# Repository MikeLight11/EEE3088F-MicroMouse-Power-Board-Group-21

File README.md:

# Micromouse Power Subsystem

## Overview
This repository contains the design files and documentation for the power subsystem of a micromouse robot developed for the EEE3088F 2025 course project. The micromouse is an autonomous robot designed to navigate through and solve mazes efficiently. The power subsystem is responsible for powering the entire micromouse, including battery management, motor control, and regulated power distribution.

## Project Description
The micromouse project consists of four main modules:
- Motherboard (provided)
- Processor (provided)
- Sensing system (provided)
- Power subsystem (this project)

Our power subsystem is designed to meet the following key requirements:
- Power and control 4 motors bidirectionally
- Provide battery monitoring via INA219 on I2C bus
- Charge the battery from 9V input with dual charging modes
- Integrate USB-C with 9V output
- Provide external load switching capabilities
- Deliver regulated 3.3V and 5V outputs
- Include ON/OFF switch with ultra-low power standby mode

## Features
- **Battery Management**: Uses BQ24074 charge controller for efficient Li-Ion battery charging with configurable charging currents (200mA standard, 600mA fast charging)
- **Motor Control**: H-bridges for bidirectional control of up to 4 motors
- **Power Regulation**: Provides stable 3.3V and 5V power rails
- **Load Switching**: Two external load switches capable of handling 1A each
- **Battery Monitoring**: INA219 current/voltage monitoring over I2C
- **Power-saving Mode**: <30μA current draw in OFF state
- **USB-C Integration**: Supports power input through USB-C

## Repository Structure
- `/Docs` - Documentation including the report
- `/Final Schematic and PCB` - KiCad schematic files and PCB design files
- `/Footprint Library` - Contains all imported footprints 
- `/Gerbers` - Production Gerber files
- `/Old Schematics` - Backup KiCad schematic files 
- `/Production files` - Contains the zip file of the Gerbers, the BOM and CPL (JLCPCB Submission files)

## Hardware Specifications
- Dimensions: Maximum 82mm × 60mm
- Battery: 3.7V 800mAh LiPo
- Input Voltage: 9V or USB-C
- Output Voltages: 3.3V (300mA max) and 5V (1.5A max)
- PCB Connector: 2x16 (2.54mm pin pitch) header connecting to the motherboard

## 3D render of PCB

## Contributors
- Michael Lighton (LGHMIC003)
- Michael Smith (SMTMIC078)

## Acknowledgments
- University of Cape Town, Department of Electrical Engineering
- EEE3088F course staff

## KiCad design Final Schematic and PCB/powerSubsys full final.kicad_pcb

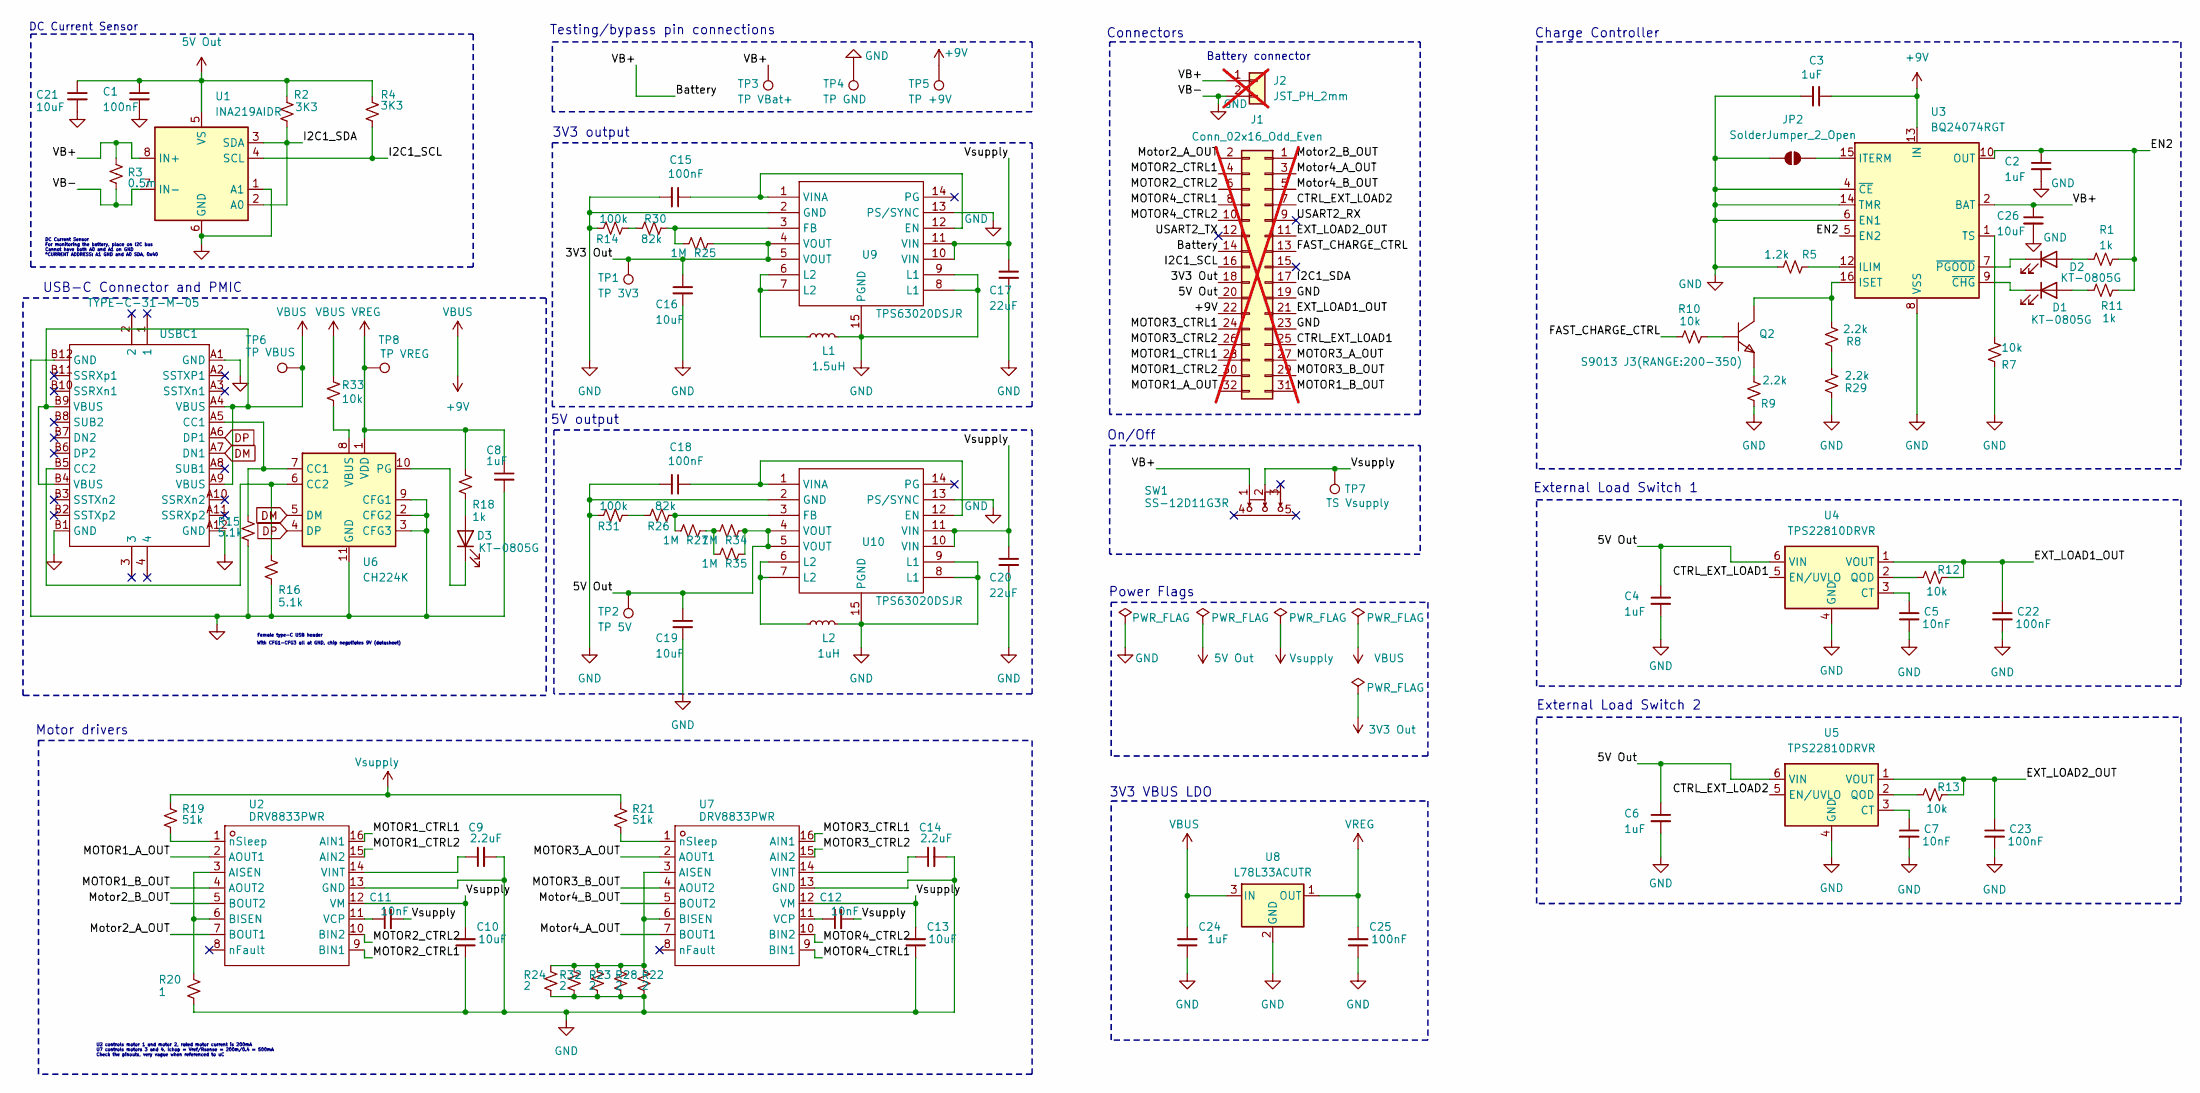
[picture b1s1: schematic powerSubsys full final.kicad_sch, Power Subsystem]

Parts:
C1, C15, C18, C22, C23, C25: 100nF; C0603; LCSC C14663
C2, C3, C4, C6, C8, C24: 1uF; C0805; LCSC C28323
C5, C7, C11, C12: 10nF; C0402; LCSC C15195
C9, C14: 2.2uF; C0805; LCSC C377773
C10, C13, C16, C19, C21, C26: 10uF; C0805; LCSC C15850
C17, C20: 22uF; C1206; LCSC C12891
D1, D2, D3: KT-0805G; LED0805-R-RD; LCSC C2297
J1: Conn_02x16_Odd_Even; PinHeader_2x16_P2.54mm_Vertical; not fitted
J2: JST_PH_2mm; JST_PH_S2B-PH-K_1x02_P2.00mm_Horizontal; not fitted
JP2: SolderJumper_2_Open; SolderJumper-2_P1.3mm_Open_RoundedPad1.0x1.5mm
L1: 1.5uH; L1008; LCSC C98034
L2: 1uH; C0805; LCSC C1042
Q2: S9013 J3(RANGE:200-350); SOT-23-3_L2.9-W1.3-P1.90-LS2.4-BR; MANUFACTURER PART S9013 J3(RANGE:200-350); LCSC PART NAME NPN 电流:500mA 耐压:25V H档(200-350)
R1, R11, R18: 1k; C0603; LCSC C21190
R2, R4: 3K3; C0603; LCSC C22978
R3: 0.5m; R2512; LCSC C469426
R5: 1.2k; C0603; LCSC C22765
R7, R10, R12, R13, R33: 10k; C0805; LCSC C17414
R8, R9, R29: 2.2k; C0603; LCSC C4190
R14, R31: 100k; C1206; LCSC C17900
R15, R16: 5.1k; C0603; LCSC C23186
R19, R21: 51k; C0805; LCSC C17737
R20: 1; C1206; LCSC C17928
R22, R23, R24, R28, R32: 2; C0603; LCSC C22977
R25, R27, R34, R35: 1M; C1206; LCSC C17927
R26, R30: 82k; C0603; LCSC C23254
SW1: SS-12D11G3R; SW-TH_SS-12D11L3; CURRENT RATING (DC) 3A; VOLTAGE RATING (DC) 125V; MANUFACTURER PART SS-12D11G3R; LCSC PART NAME 柄长3mm 弯插双档 滑动开关
TP1: TP 3V3; TestPoint_Pad_D1.5mm
TP2: TP 5V; TestPoint_Pad_D1.5mm
TP3: TP VBat+; TestPoint_Pad_D1.5mm
TP4: TP GND; TestPoint_Pad_D1.5mm
TP5: TP +9V; TestPoint_Pad_D1.5mm
TP6: TP VBUS; TestPoint_Pad_D1.5mm
TP7: TS Vsupply; TestPoint_Pad_D1.5mm
TP8: TP VREG; TestPoint_Pad_D1.5mm
U1: INA219AIDR; SOIC-8_3.9x4.9mm_P1.27mm; LCSC C138706
U2, U7: DRV8833PWR; TSSOP-16_L5.0-W4.4-P0.65-LS6.4-BL; MANUFACTURER PART DRV8833PWR; LCSC PART NAME DRV8833PWR
U3: BQ24074RGT; VQFN-16-1EP_3x3mm_P0.5mm_EP1.6x1.6mm; LCSC C54313
U4, U5: TPS22810DRVR; WSON-6-1EP_2x2mm_P0.65mm_EP1x1.6mm; LCSC C527679
U6: CH224K; SSOP-10-1EP_3.9x4.9mm_P1mm_EP2.1x3.3mm; LCSC C970725
U8: L78L33ACUTR; SOT-89-3; LCSC C14170
U9, U10: TPS63020DSJR; VSON-14_L4.0-W3.0-P0.50-BL-EP_TI_DSJ; INPUT VOLTAGE 1.8V~5.5V; OUTPUT VOLTAGE 1.2V~5.5V; MANUFACTURER PART TPS63020DSJR; LCSC PART NAME 高效率单电感升降压转换器
USBC1: TYPE-C-31-M-05; USB-C-SMD_TYPE-C-USB-19; CURRENT RATING-POWER 5A; MANUFACTURER PART TYPE-C-31-M-05; LCSC PART NAME Type-C 母

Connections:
3V3 Out: C16.1, J1.18, R25.2, TP1.1, U9.4 (VOUT), U9.5 (VOUT)
5V Out: C1.1, C4.1, C6.1, C19.1, C21.1, J1.20, R2.1, R4.1, R34.2, R35.2, TP2.1, U1.5 (VS), U4.6 (VIN), U5.6 (VIN), U10.4 (VOUT), U10.5 (VOUT)
+9V: C3.1, C24.2, J1.22, R33.1, TP5.1, TP6.1, U3.13 (IN), U8.3 (IN), USBC1.A4 (VBUS), USBC1.A9 (VBUS), USBC1.B4 (VBUS), USBC1.B9 (VBUS)
/Battery: C26.1, J1.14, J2.1, R3.1, SW1.1, TP3.1, U1.8 (IN+), U3.2 (BAT), U3.3 (BAT)
/CTRL_EXT_LOAD1: J1.25, U4.5 (EN/UVLO)
/CTRL_EXT_LOAD2: J1.7, U5.5 (EN/UVLO)
/EN2: C2.1, R1.1, R11.1, U3.5 (EN2), U3.10 (OUT), U3.11 (OUT)
/EXT_LOAD1_OUT: C22.1, J1.21, R12.2, U4.1 (VOUT)
/EXT_LOAD2_OUT: C23.1, J1.11, R13.2, U5.1 (VOUT)
/FAST_CHARGE_CTRL: J1.13, R10.1
/I2C1_SCL: J1.16, R4.2, U1.4 (SCL)
/I2C1_SDA: J1.17, R2.2, U1.2 (A0), U1.3 (SDA)
/MOTOR1_A_OUT: J1.32, U2.2 (AOUT1)
/MOTOR1_B_OUT: J1.31, U2.4 (AOUT2)
/MOTOR1_CTRL1: J1.28, U2.16 (AIN1)
/MOTOR1_CTRL2: J1.30, U2.15 (AIN2)
/MOTOR2_CTRL1: J1.4, U2.9 (BIN1)
/MOTOR2_CTRL2: J1.6, U2.10 (BIN2)
/MOTOR3_A_OUT: J1.27, U7.2 (AOUT1)
/MOTOR3_B_OUT: J1.29, U7.4 (AOUT2)
/MOTOR3_CTRL1: J1.24, U7.16 (AIN1)
/MOTOR3_CTRL2: J1.26, U7.15 (AIN2)
/MOTOR4_CTRL1: J1.8, U7.9 (BIN1)
/MOTOR4_CTRL2: J1.10, U7.10 (BIN2)
/Motor2_A_OUT: J1.2, U2.7 (BOUT1)
/Motor2_B_OUT: J1.1, U2.5 (BOUT2)
/Motor4_A_OUT: J1.3, U7.7 (BOUT1)
/Motor4_B_OUT: J1.5, U7.5 (BOUT2)
/USART2_RX: J1.9
/USART2_TX: J1.12
DM: U6.5 (DM), USBC1.A7 (DN1)
DP: U6.4 (DP), USBC1.A6 (DP1)
GND: C1.2, C2.2, C3.2, C4.2, C5.2, C6.2, C7.2, C8.2, C9.2, C10.1, C13.1, C14.2, C15.2, C16.2, C17.2, C18.2, C19.2, C20.2, C21.2, C22.2, C23.2, C24.1, C25.1, C26.2, J1.19, J1.23, J2.2, JP2.1 (A), L1.2, L2.2, R3.2, R5.1, R7.2, R9.2, R14.1, R15.2, R16.2, R20.2, R22.2, R23.2, R24.2, R28.2, R29.2, R31.1, R32.2, TP4.1, U1.1 (A1), U1.6 (GND), U1.7 (IN-), U2.13 (GND), U3.4 (~CE), U3.6 (EN1), U3.8 (VSS), U3.14 (TMR), U3.17 (VSS), U4.4 (GND), U4.7 (GND), U5.4 (GND), U5.7 (GND), U6.2 (CFG2), U6.3 (CFG3), U6.9 (CFG1), U6.11 (GND), U7.13 (GND), U8.2 (GND), U9.2 (GND), U9.8 (L1), U9.9 (L1), U9.13 (PS/SYNC), U9.15 (PGND), U10.2 (GND), U10.8 (L1), U10.9 (L1), U10.13 (PS/SYNC), U10.15 (PGND), USBC1.A1 (GND), USBC1.A12 (GND), USBC1.B1 (GND), USBC1.B12 (GND); also elsewhere on the board
unnamed: D1.2 (A), R11.2
unnamed: D1.1 (K), U3.9 (~CHG)
unnamed: D2.2 (A), R1.2
unnamed: D2.1 (K), U3.7 (~PGOOD)
unnamed: D3.2 (A), R18.2
unnamed: D3.1 (K), U6.10 (PG)
unnamed: JP2.2 (B), U3.15 (ITERM)
unnamed: L1.1, U9.6 (L2), U9.7 (L2)
unnamed: L2.1, U10.6 (L2), U10.7 (L2)
unnamed: Q2.1 (B), R10.2
unnamed: Q2.3 (C), R8.1, U3.16 (ISET)
unnamed: Q2.2 (E), R9.1
unnamed: R14.2, R30.1
unnamed: R26.1, R31.2
unnamed: R27.2, R34.1, R35.1
unnamed: R8.2, R29.1
unnamed: R20.1, U2.3 (AISEN), U2.6 (BISEN)
unnamed: C11.1, U2.11 (VCP)
unnamed: C9.1, U2.14 (VINT)
unnamed: R19.2, U2.1 (nSleep)
unnamed: R5.2, U3.12 (ILIM)
unnamed: R7.1, U3.1 (TS)
unnamed: C5.1, U4.3 (CT)
unnamed: R12.1, U4.2 (QOD)
unnamed: C7.1, U5.3 (CT)
unnamed: R13.1, U5.2 (QOD)
unnamed: R15.1, U6.7 (CC1), USBC1.A5 (CC1)
unnamed: R16.1, U6.6 (CC2), USBC1.B5 (CC2)
unnamed: R33.2, U6.8 (VBUS)
unnamed: R22.1, R23.1, R24.1, R28.1, R32.1, U7.3 (AISEN), U7.6 (BISEN)
unnamed: C12.1, U7.11 (VCP)
unnamed: C14.1, U7.14 (VINT)
unnamed: R21.2, U7.1 (nSleep)
unnamed: C15.1, U9.1 (VINA), U9.12 (EN)
unnamed: R25.1, R30.2, U9.3 (FB)
unnamed: C18.1, U10.1 (VINA), U10.12 (EN)
unnamed: R26.2, R27.1, U10.3 (FB)
VREG: C8.1, C25.2, R18.1, TP8.1, U6.1 (VDD), U8.1 (OUT)
Vsupply: C10.2, C11.2, C12.2, C13.2, C17.1, C20.1, R19.1, R21.1, SW1.2, TP7.1, U2.12 (VM), U7.12 (VM), U9.10 (VIN), U9.11 (VIN), U10.10 (VIN), U10.11 (VIN)

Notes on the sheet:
Battery connector
3V3 VBUS LDO
U2 controls motor 1 and motor 2, rated motor current is 200mA U7 controls motors 3 and 4, Ichop = Vref/Rsense = 200m/0.4 = 500mA Check the pinouts, very vague when referenced to uC
DC Current Sensor
External Load Switch 2
Connectors
DC Current Sensor For monitoring the battery, place on I2C bus Cannot have both A0 and A1 on GND *CURRENT ADDRESS: A1 GND and A0 SDA, 0x40
Power Flags
Motor drivers
Charge Controller
Female type-C USB header
3V3 output
On/Off
5V output
Testing/bypass pin connections
With CFG1-CFG3 all at GND, chip negotiates 9V (datasheet)
External Load Switch 1
USB-C Connector and PMIC

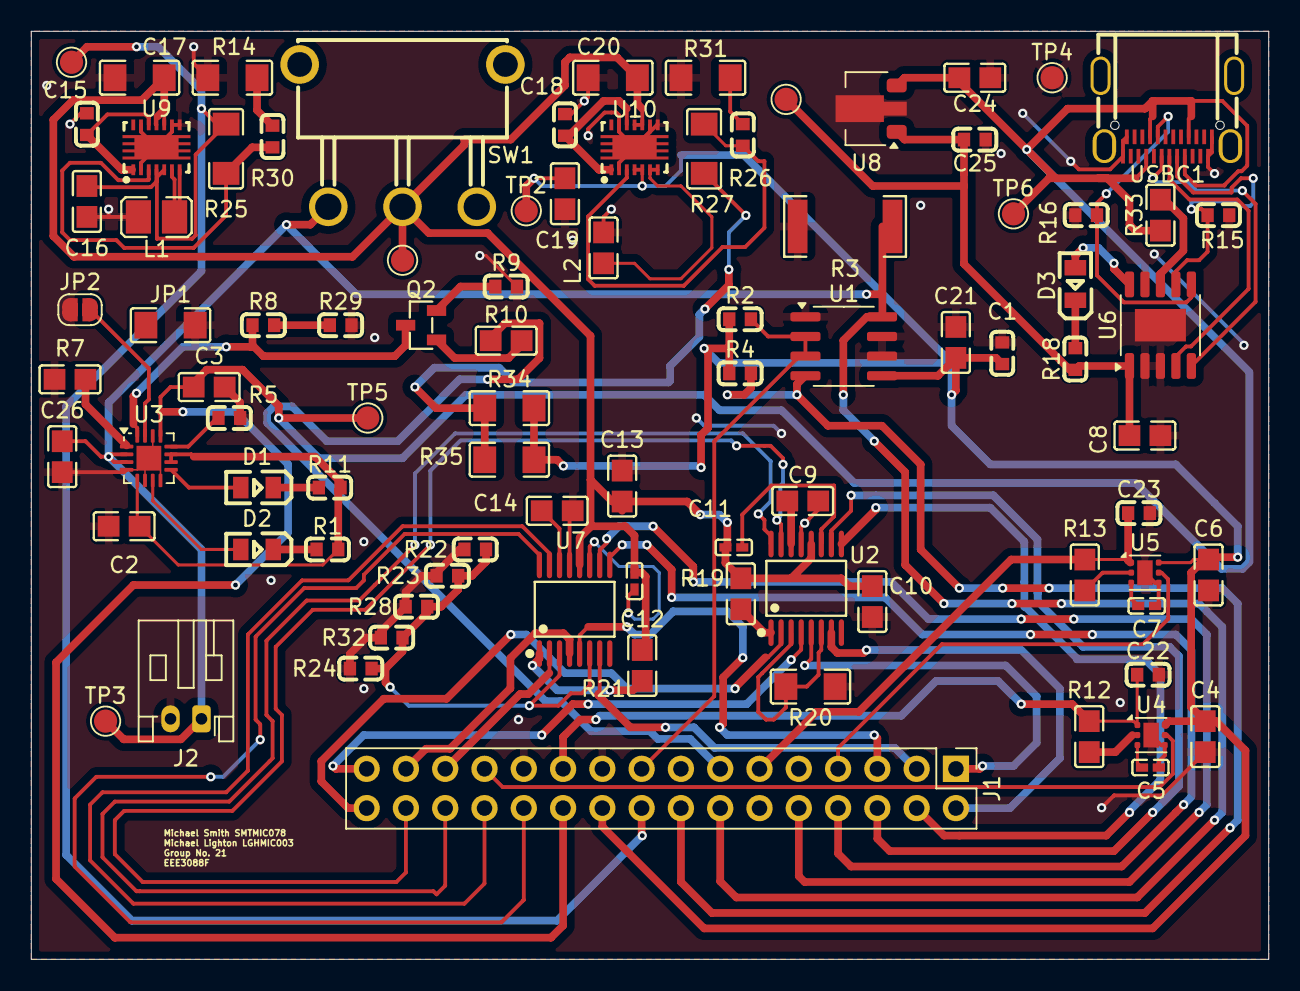
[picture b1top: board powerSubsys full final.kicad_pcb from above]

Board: 2 copper layers, 80.0 x 60.0 mm, 89 parts (0 on the bottom side), 70 nets.

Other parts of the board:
JP1: JP RITERM; C1206

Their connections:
GND: JP1.1 (A); also elsewhere on the board

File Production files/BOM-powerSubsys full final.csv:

Comment,Designator,Footprint,LCSC,Quantity
1uH,L2,C0805,C1042,1
22uF,"C17,C20",C1206,C12891,2
INA219AIDR,U1,SOIC-8_3.9x4.9mm_P1.27mm,C138706,1
L78L33ACUTR,U8,SOT-89-3,C14170,1
100nF,"C1,C15,C18,C22,C23,C25",C0603,C14663,6
10nF,"C11,C12,C5,C7",C0402,C15195,4
10uF,"C10,C13,C16,C19,C21,C26",C0805,C15850,6
10k,"R10,R12,R13,R33,R7",C0805,C17414,5
51k,"R19,R21",C0805,C17737,2
100k,"R14,R31",C1206,C17900,2
1M,"R25,R27,R34,R35",C1206,C17927,4
1,R20,C1206,C17928,1
1k,"R1,R11,R18",C0603,C21190,3
1.2k,R5,C0603,C22765,1
KT-0805G,"D1,D2,D3",LED0805-R-RD,C2297,3
2,"R22,R23,R24,R28,R32",C0603,C22977,5
3K3,"R2,R4",C0603,C22978,2
5.1k,"R15,R16",C0603,C23186,2
82k,"R26,R30",C0603,C23254,2
1uF,"C2,C24,C3,C4,C6,C8",C0805,C28323,6
2.2uF,"C14,C9",C0805,C377773,2
2.2k,"R29,R8,R9",C0603,C4190,3
0.5m,R3,R2512,C469426,1
TPS22810DRVR,"U4,U5",WSON-6-1EP_2x2mm_P0.65mm_EP1x1.6mm,C527679,2
DRV8833PWR,"U2,U7",TSSOP-16_L5.0-W4.4-P0.65-LS6.4-BL,C544801,2
S9013 J3(RANGE:200-350),Q2,SOT-23-3_L2.9-W1.3-P1.90-LS2.4-BR,C6749,1
SS-12D11G3R,SW1,SW-TH_SS-12D11L3,C843362,1
TYPE-C-31-M-05,USBC1,USB-C-SMD_TYPE-C-USB-19,C845581,1
CH224K,U6,SSOP-10-1EP_3.9x4.9mm_P1mm_EP2.1x3.3mm,C970725,1
1.5uH,L1,L1008,C98034,1
JP RITERM,JP1,C1206,,1
TPS63020DSJR,U9,VSON-14_L4.0-W3.0-P0.50-BL-EP_TI_DSJ,,1
TPS63020DSJR,U10,VSON-14_L4.0-W3.0-P0.50-BL-EP_TI_DSJ,,1
BQ24074RGT,U3,VQFN-16-1EP_3x3mm_P0.5mm_EP1.6x1.6mm,,1

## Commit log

2025-03-12 Create Design requirements file added
2025-03-12 Ranked Design requirements
2025-03-17 ChatGPT'd Updated Design requirements
2025-03-17 Created Smith design
2025-03-17 Updated Smith design
2025-03-17 Create Lighto's Requirements
2025-03-19 Update Smith design v3
2025-03-19 Add files via upload
    Rev 1 of Kicad design:
    Created file
    Added connectors
    Added connector headings
    Started DC current monitor functionality
2025-03-21 Add files via upload
    - Progressed INA219 current sensor
    - Set new I2C address config to not conflict with sensor module
    - Neatened up design
2025-03-22 Added the charging controller
2025-03-23 Added: Charge Controller and Load Switches
2025-03-23 Add files via upload
    Added: USB-C female header and PWIC
2025-03-24 Cleaning and addition
    Cleaned up schematic
    Added H-bridge IC
2025-03-25 Added motor drivers
2025-03-25 Deleted powerSubsys (2).kicad_sch
2025-03-25 Added: Voltage converters and Switch
2025-03-26 Added 3V3 and 5V Output
2025-03-26 Updated the switch design
2025-03-26 Updated the load switches
2025-03-26 Footprints
2025-03-26 Added power flags
2025-03-27 Kicad footies
2025-03-27 Added voltage regulator
2025-03-27 Final
2025-03-28 this is a zip of the schematic and pcb
2025-04-21 Create Schematics
2025-04-21 Rename powerSubsys full final.kicad_prl to Final KiCad files/powerSubsys full final.kicad_prl
2025-04-21 Rename powerSubsys full final.csv to Final KiCad files/powerSubsys full final.csv
2025-04-21 Rename powerSubsys full final.kicad_pro to Final KiCad files/powerSubsys full final.kicad_pro
2025-04-21 Update and rename powerSubsys full.kicad_sch-bak to Final KiCad files/powerSubsys full.kicad_sch-bak
2025-04-21 Rename Design requirements to Docs/Design requirements
2025-04-21 Rename Library.pretty.zip to Footprint Libary/Library.pretty.zip
2025-04-21 Rename Final Power System.zip to Final KiCad files/Final Power System.zip
2025-04-22 Folder that contains imported footprints from JLCPCB
2025-04-24 Create txt
